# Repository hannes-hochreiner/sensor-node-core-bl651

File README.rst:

Sensor Node Core BL651
======================

A sensor node for the SensorNet project, based on the BL651 module.

Wire
----

AWG 23 / 0.573 mm diameter / 0.258 mm² area

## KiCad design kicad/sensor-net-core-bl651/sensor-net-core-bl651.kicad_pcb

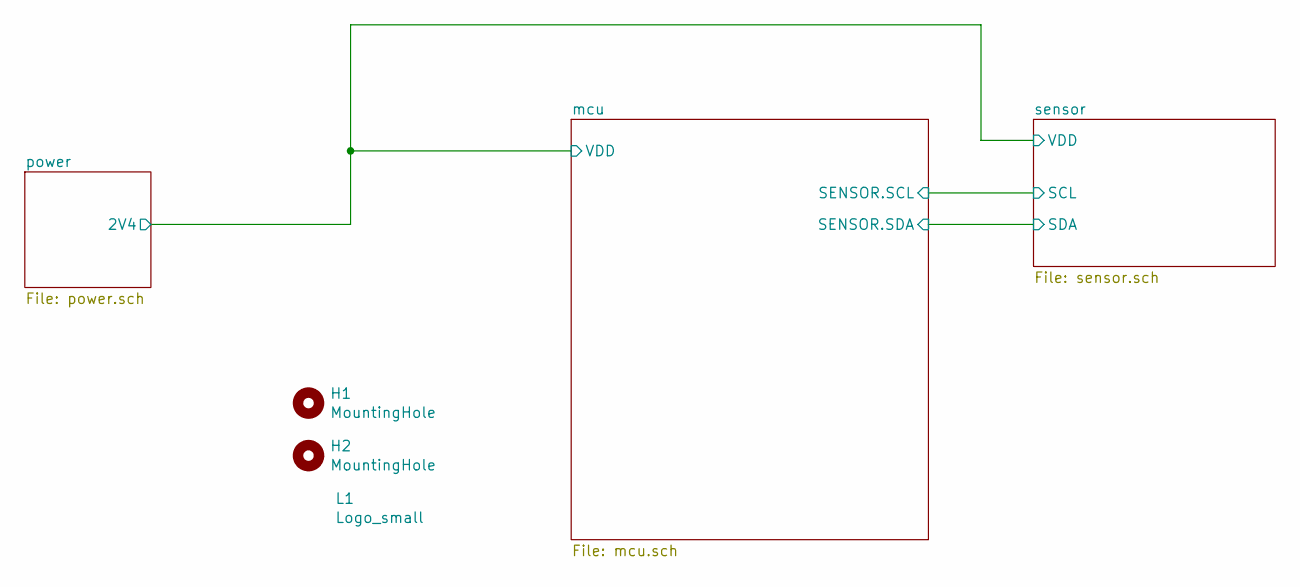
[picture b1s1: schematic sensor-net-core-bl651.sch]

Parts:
H1, H2: MountingHole; MountingHole_2.2mm_M2_Pad_Via
L1: Logo_small; logo_small

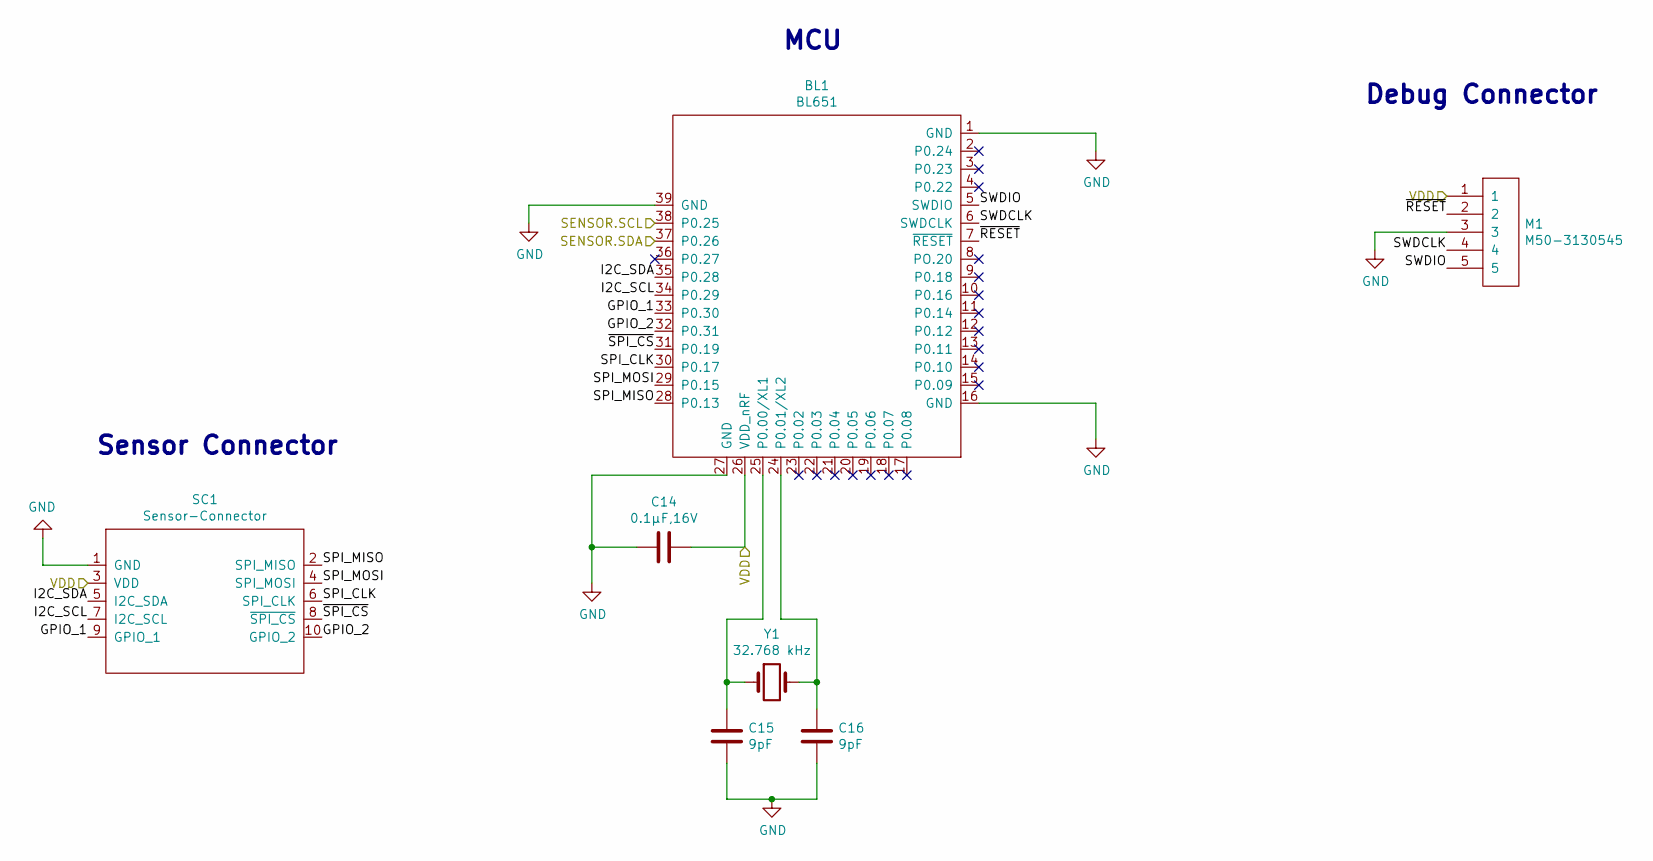
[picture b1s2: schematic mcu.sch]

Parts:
BL1: BL651; Manufacturer Part Number 453-00005; Digi-Key Part Number 453-00005CT-ND
C14: 0.1µF,16V; C_0603_1608Metric
C15, C16: 9pF; C_0603_1608Metric; Manufacturer Part Number CC0603CRNPO9BN9R0; Digi-Key Part Number 311-3866-1-ND
M1: M50-3130545; Manufacturer_PartNumber M50-3130545; DigiKey_PartNumber 952-3585-ND
SC1: Sensor-Connector; Sensor-Connector_M50-3150542R; Manufacturer Part Number M50-3150542R; Digi-Key Part Number 952-3493-1-ND
Y1: 32.768 kHz; Crystal_SMD_MicroCrystal_CC7V-T1A-2Pin_3.2x1.5mm; Manufacturer Part Number CM7V-T1A-32.768KHZ-9PF-10PPM-TA-QC; Digi-Key Part Number 2195-CM7V-T1A-32.768KHZ-9PF-10PPM-TA-QC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

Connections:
/mcu/GPIO_1: BL1.33 (P0.30), SC1.9 (GPIO_1)
/mcu/GPIO_2: BL1.32 (P0.31), SC1.10 (GPIO_2)
/mcu/I2C_SCL: BL1.34 (P0.29), SC1.7 (I2C_SCL)
/mcu/I2C_SDA: BL1.35 (P0.28), SC1.5 (I2C_SDA)
/mcu/SPI_CLK: BL1.30 (P0.17), SC1.6 (SPI_CLK)
/mcu/SPI_MISO: BL1.28 (P0.13), SC1.2 (SPI_MISO)
/mcu/SPI_MOSI: BL1.29 (P0.15), SC1.4 (SPI_MOSI)
/mcu/SWDCLK: BL1.6 (SWDCLK), M1.4
/mcu/SWDIO: BL1.5 (SWDIO), M1.5
/mcu/~RESET: BL1.7 (~RESET), M1.2
/mcu/~SPI_CS: BL1.31 (P0.19), SC1.8 (~SPI_CS)
/power/2V4: BL1.26 (VDD_nRF), C14.1, M1.1, SC1.3 (VDD); also elsewhere on the board
/sensor/SCL: BL1.38 (P0.25); also elsewhere on the board
/sensor/SDA: BL1.37 (P0.26); also elsewhere on the board
GND: BL1.1 (GND), BL1.16 (GND), BL1.27 (GND), BL1.39 (GND), C14.2, C15.2, C16.2, M1.3, SC1.1 (GND); also elsewhere on the board
unnamed: BL1.24 (P0.01/XL2), C16.1, Y1.2
unnamed: BL1.25 (P0.00/XL1), C15.1, Y1.1

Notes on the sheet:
Sensor Connector
MCU
Debug Connector

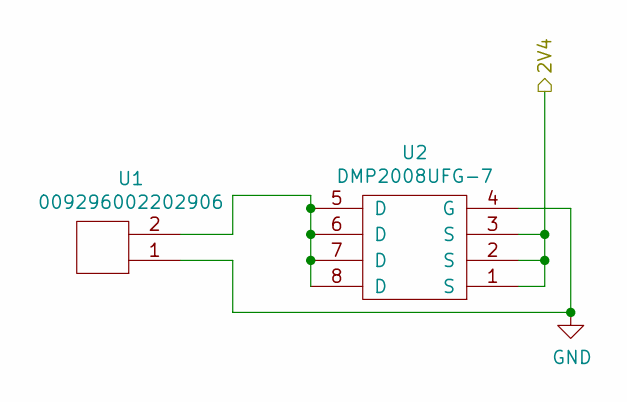
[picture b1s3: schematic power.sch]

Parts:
U1: 009296002202906; Manufacturer Part Number 009296002202906; Digi-Key Part Number 478-9533-1-ND
U2: DMP2008UFG-7; Manufacturer Part Number DMP2008UFG-7; Digi-Key Part Number DMP2008UFG-7DICT-ND

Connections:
/power/2V4: U2.1 (S), U2.2 (S), U2.3 (S); also elsewhere on the board
GND: U1.1, U2.4 (G); also elsewhere on the board
unnamed: U1.2, U2.5 (D), U2.6 (D), U2.7 (D), U2.8 (D)

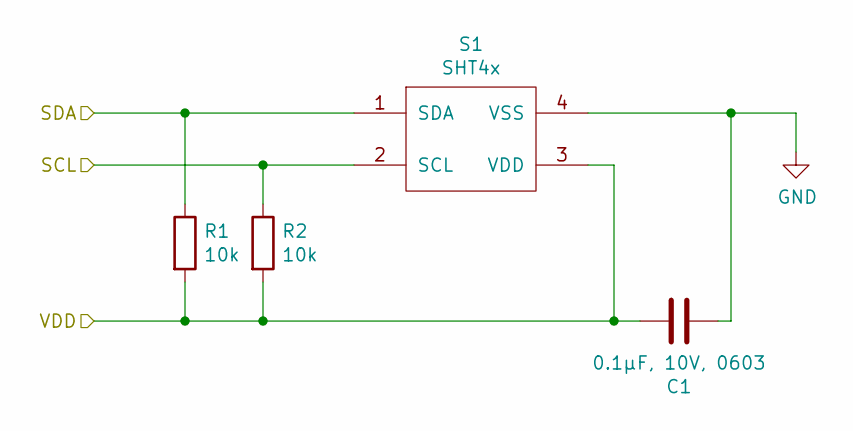
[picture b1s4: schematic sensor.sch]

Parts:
C1: 0.1µF, 10V, 0603; C_0603_1608Metric
R1, R2: 10k; R_0603_1608Metric
S1: SHT4x; Manufacturer Part Number SHT40-AD1B-R2; Digi-Key Part Number 1649-SHT40-AD1B-R2CT-ND

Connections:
/power/2V4: C1.1, R1.2, R2.2, S1.3 (VDD); also elsewhere on the board
/sensor/SCL: R2.1, S1.2 (SCL); also elsewhere on the board
/sensor/SDA: R1.1, S1.1 (SDA); also elsewhere on the board
GND: C1.2, S1.4 (VSS); also elsewhere on the board

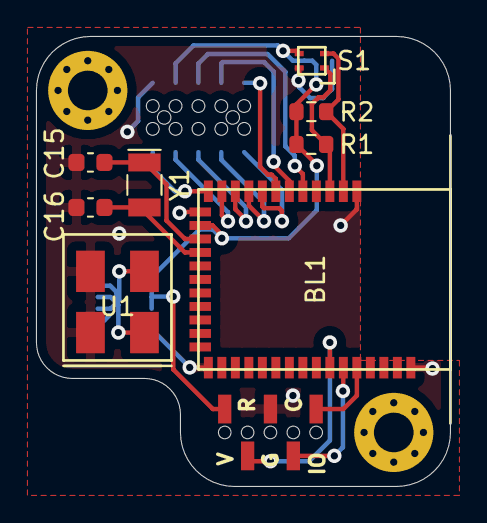
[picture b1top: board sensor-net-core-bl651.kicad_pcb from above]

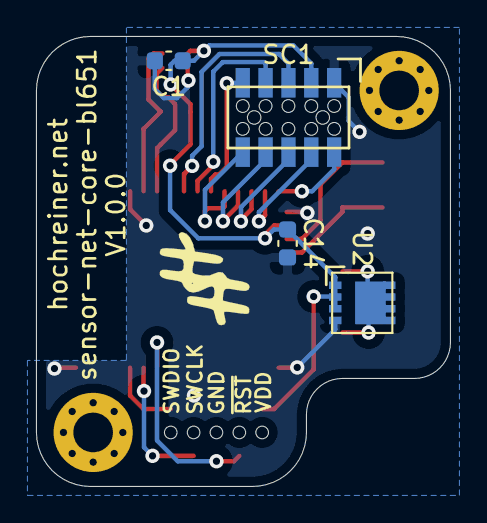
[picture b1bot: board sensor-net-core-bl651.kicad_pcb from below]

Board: 2 copper layers, 23.0 x 25.0 mm, 16 parts (5 on the bottom side), 18 nets.

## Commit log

2021-01-03 fix README
